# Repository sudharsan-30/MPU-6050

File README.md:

# MPU-6050
A full Kicad module of pysical project about the MPU-6050 is a popular, low-cost 6-axis motion tracking sensor. It combines a 3-axis accelerometer and a 3-axis gyroscope. It uses standard I2C communication and is widely used in DIY projects like drones, balancing robots, and digital levels.
# MPU-6050 KiCad Hardware Design

A full KiCad hardware design project for the **MPU-6050**—a popular, low-cost 6-axis Motion Tracking Device combining a 3-axis accelerometer and a 3-axis gyroscope.

---

## 📌 Features & Overview

* **Sensor:** MPU-6050 (3-Axis Accelerometer + 3-Axis Gyroscope)
* **Communication Protocol:** Standard $I^2C$ Interface
* **Applications:** DIY Electronics, Drones, Self-Balancing Robots, Digital Levels, and Motion-Tracking Devices
* **EDA Tool:** KiCad PCB Design Suite

---

## 📁 Repository Structure

```text
├── new_MPU/               # Primary KiCad project directory
├── new_MPU.kicad_pcb      # KiCad PCB Layout file
└── README.md              # Project documentation

How to Use This Project
Clone the Repository:

Bash
git clone [https://github.com/sudharsan-30/MPU-6050.git](https://github.com/sudharsan-30/MPU-6050.git)
Open in KiCad:

Launch KiCad (v7.0 or higher recommended).

Open the .kicad_pcb or project file located in the project folder to view and edit the PCB layout and schematic.

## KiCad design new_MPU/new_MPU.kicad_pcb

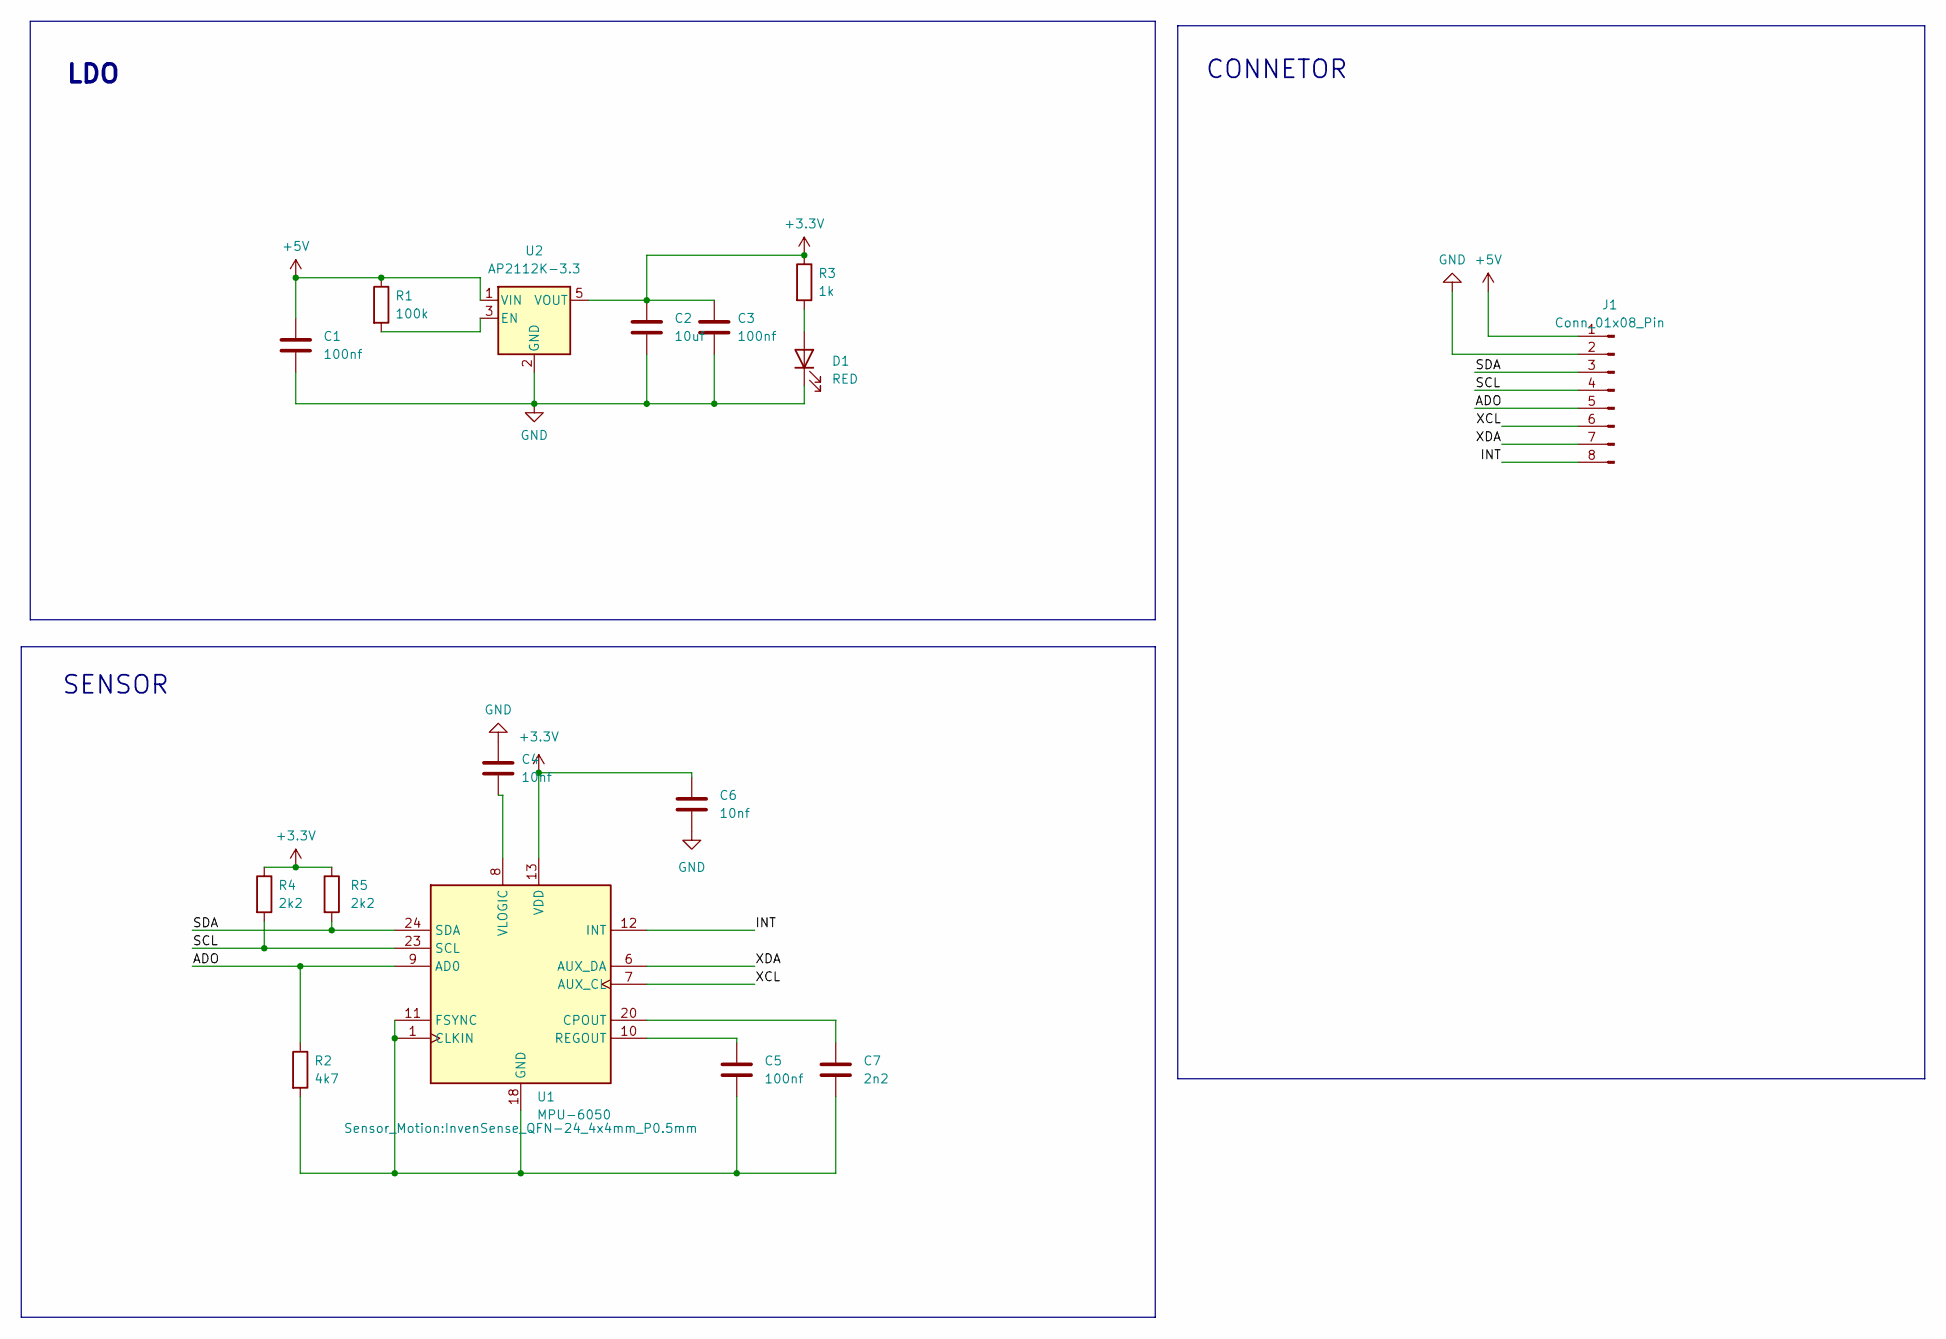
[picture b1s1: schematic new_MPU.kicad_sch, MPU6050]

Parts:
C1, C3, C5: 100nf; C_0603_1608Metric
C2: 10uf; C_0805_2012Metric
C4: 10nf; C_0805_2012Metric
C6: 10nf; C_0603_1608Metric
C7: 2n2; C_0603_1608Metric
D1: RED; LED_0603_1608Metric
J1: Conn_01x08_Pin; PinHeader_1x08_P2.54mm_Vertical
R1: 100k; R_0603_1608Metric
R2: 4k7; R_0603_1608Metric
R3: 1k; R_0603_1608Metric
R4, R5: 2k2; R_0603_1608Metric
U1: MPU-6050; InvenSense_QFN-24_4x4mm_P0.5mm
U2: AP2112K-3.3; SOT-23-5

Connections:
+3.3V: C2.1, C3.1, C6.1, R3.1, R4.1, R5.1, U1.13 (VDD), U2.5 (VOUT)
+5V: C1.1, J1.1, R1.1, U2.1 (VIN)
/ADO: J1.5, R2.1, U1.9 (AD0)
/INT: J1.8, U1.12 (INT)
/SCL: J1.4, R4.2, U1.23 (SCL)
/SDA: J1.3, R5.2, U1.24 (SDA)
/XCL: J1.6, U1.7 (AUX_CL)
/XDA: J1.7, U1.6 (AUX_DA)
GND: C1.2, C2.2, C3.2, C4.1, C6.2, D1.1 (K), J1.2, U2.2 (GND)
unnamed: D1.2 (A), R3.2
unnamed: C5.2, C7.2, R2.2, U1.1 (CLKIN), U1.11 (FSYNC), U1.18 (GND)
unnamed: C7.1, U1.20 (CPOUT)
unnamed: C5.1, U1.10 (REGOUT)
unnamed: C4.2, U1.8 (VLOGIC)
unnamed: R1.2, U2.3 (EN)

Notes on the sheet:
SENSOR
LDO
CONNETOR

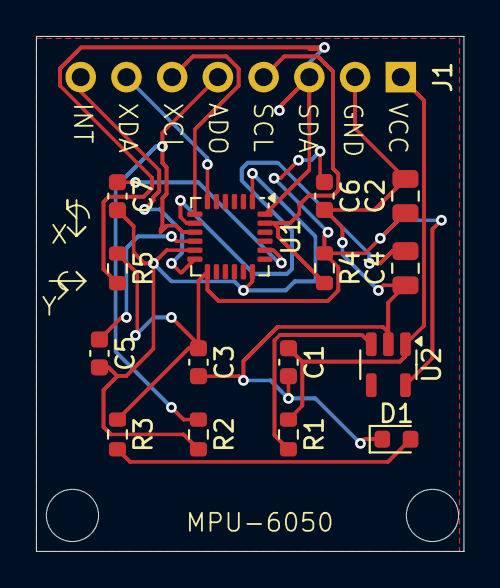
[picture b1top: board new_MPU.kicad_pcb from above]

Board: 2 copper layers, 23.8 x 28.6 mm, 16 parts (0 on the bottom side), 15 nets.
